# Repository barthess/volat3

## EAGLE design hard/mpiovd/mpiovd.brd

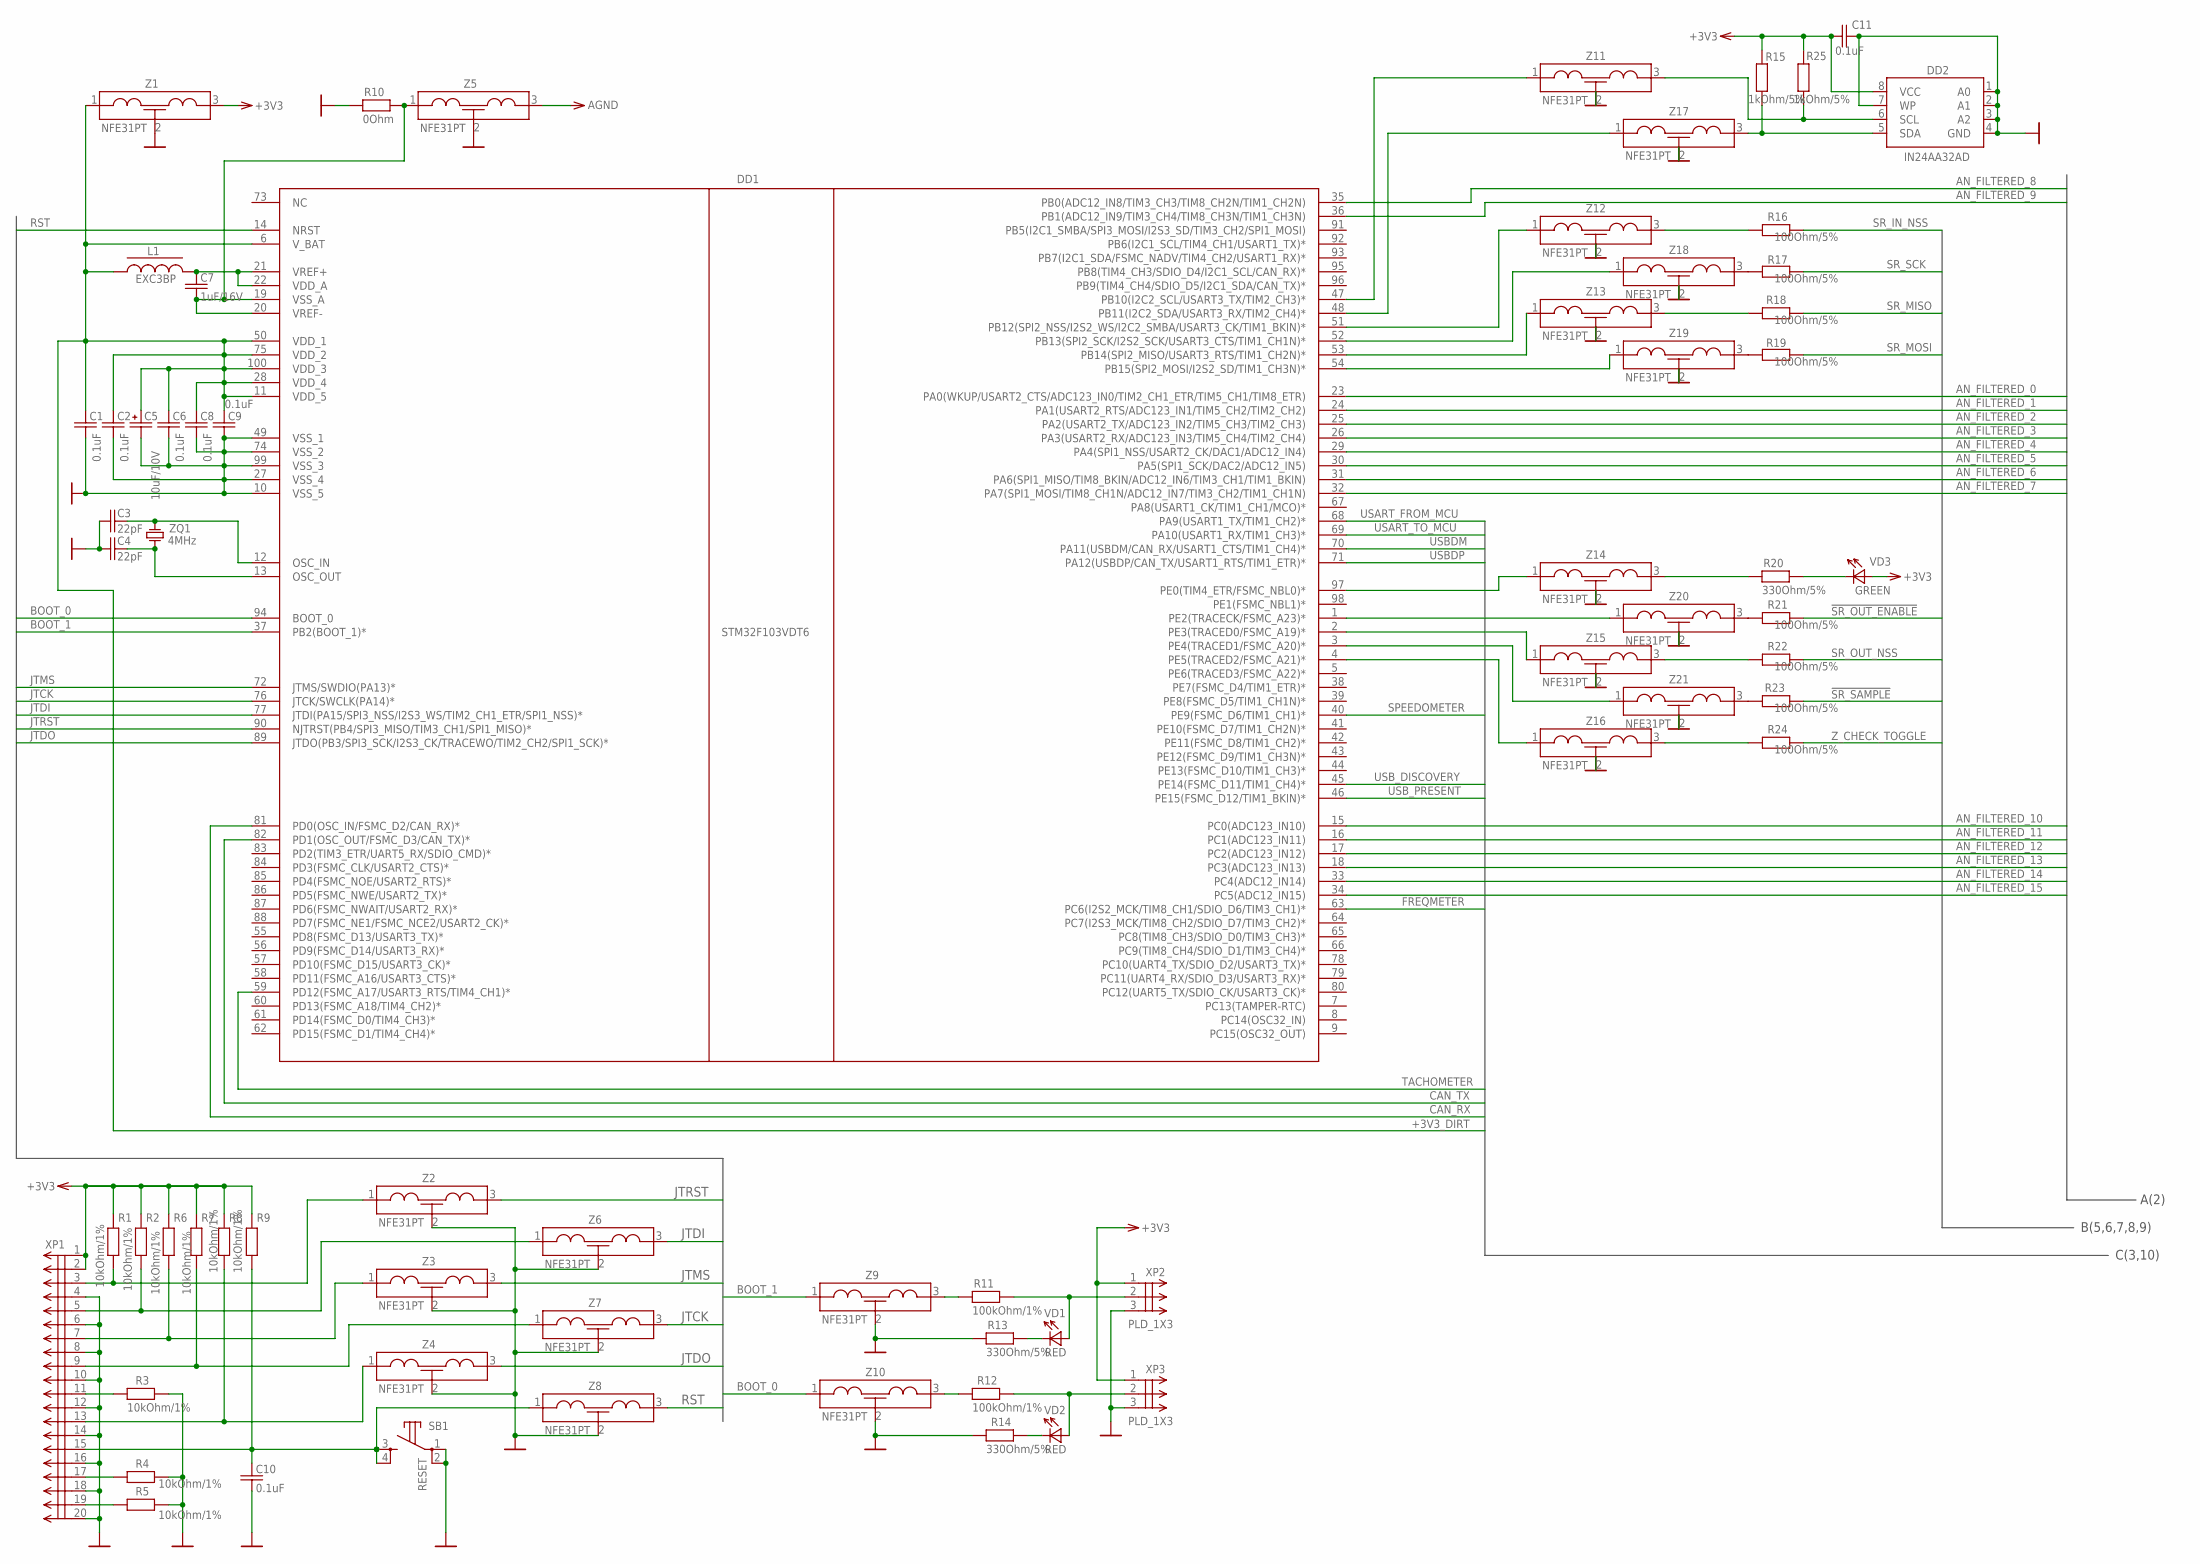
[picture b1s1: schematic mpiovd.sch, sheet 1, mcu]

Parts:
C1, C2, C6, C8, C9, C10, C11: 0.1uF; C0603; PARTNO C0603C104K5RACTU
C3, C4: 22pF; C0603; PARTNO C0603C220J5GACTU
C5: 10uF/10V; A/3216-18W; PARTNO T491A106K010AT
C7: 1uF/16V; C0603; PARTNO C0603C105K4PACTU
DD1: STM32F103VDT6; TQFP100; PARTNO STM32F103VDT6
DD2: IN24AA32AD; SO08; PARTNO IN24AA32AD
L1: EXC3BP; L0603; PARTNO EXC3BP121H
R1, R2, R3, R4, R5, R6, R7, R8, R9: 10kOhm/1%; R0603; PARTNO RC0603FR-1010KL
R10: 0Ohm; R0805; PARTNO ERJ6GEY0R00V
R11, R12: 100kOhm/1%; R0603; PARTNO RC0603FR-13100KL
R13, R14, R20: 330Ohm/5%; R0603; PARTNO ERJ3GEYJ331V
R15, R25: 1kOhm/5%; R0805; PARTNO ERJ6GEYJ102V
R16, R17, R18, R19, R21, R22, R23, R24: 100Ohm/5%; R0603; PARTNO ERJ3GEYJ101V
SB1: RESET; B3S-10XX; PARTNO 4-1437565-2
VD1, VD2: RED; LED-0805; PARTNO KPHCM-2012EC-T
VD3: GREEN; LED-0805; PARTNO KPHCM-2012SGC-T
XP1: PLD_2X10-SHROUDED; PLD_2X10_SHROUDED; PARTNO MC9A12-2034
XP2, XP3: PLD_1X3; PLD_1X03; PARTNO 825433-3
Z1, Z2, Z3, Z4, Z5, Z6, Z7, Z8, Z9, Z10, Z11, Z12, Z13, Z14, Z15, Z16, Z17, Z18, Z19, Z20, Z21: NFE31PT; NFE31; PARTNO NFE31PT152Z1E9
ZQ1: 4MHz; HC49U-V; PARTNO CA-4.000-18-3050-X

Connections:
!SR_OUT_ENABLE: R21.1; also elsewhere on the board
!SR_SAMPLE: R23.1; also elsewhere on the board
+3V3: C11.2, DD2.8 (VCC), R1.2, R2.2, R6.2, R7.2, R8.2, R9.2, R15.1, R25.1, VD3.A, XP1.1, XP1.2, XP2.1, XP3.1, Z1.3; also elsewhere on the board
+3V3_DIRT: C1.1, C2.1, C5.+, C6.1, C8.1, C9.1, DD1.6 (V_BAT), DD1.11 (VDD_5), DD1.28 (VDD_4), DD1.50 (VDD_1), DD1.75 (VDD_2), DD1.100 (VDD_3), L1.1, Z1.1; also elsewhere on the board
AGND: Z5.3; also elsewhere on the board
AN_FILTERED_0: DD1.23 (PA0(WKUP/USART2_CTS/ADC123_IN0/TIM2_CH1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); also elsewhere on the board
AN_FILTERED_1: DD1.24 (PA1(USART2_RTS/ADC123_IN1/TIM5_CH2/TIM2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); also elsewhere on the board
AN_FILTERED_2: DD1.25 (PA2(USART2_TX/ADC123_IN2/TIM5_CH3/TIM2_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); also elsewhere on the board
AN_FILTERED_3: DD1.26 (PA3(USART2_RX/ADC123_IN3/TIM5_CH4/TIM2_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); also elsewhere on the board
AN_FILTERED_4: DD1.29 (PA4(SPI1_NSS/USART2_CK/DAC1/ADC12_IN4)); also elsewhere on the board
AN_FILTERED_5: DD1.30 (PA5(SPI1_SCK/DAC2/ADC12_IN5)); also elsewhere on the board
AN_FILTERED_6: DD1.31 (PA6(SPI1_MISO/TIM8_BKIN/ADC12_IN6/TIM3_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); also elsewhere on the board
AN_FILTERED_7: DD1.32 (PA7(SPI1_MOSI/TIM8_CH1N/ADC12_IN7/TIM3_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); also elsewhere on the board
AN_FILTERED_8: DD1.35 (PB0(ADC12_IN8/TIM3_CH3/TIM8_CH2N/TIM1_C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); also elsewhere on the board
AN_FILTERED_9: DD1.36 (PB1(ADC12_IN9/TIM3_CH4/TIM8_CH3N/TIM1_C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); also elsewhere on the board
AN_FILTERED_10: DD1.15 (PC0(ADC123_IN10)); also elsewhere on the board
AN_FILTERED_11: DD1.16 (PC1(ADC123_IN11)); also elsewhere on the board
AN_FILTERED_12: DD1.17 (PC2(ADC123_IN12)); also elsewhere on the board
AN_FILTERED_13: DD1.18 (PC3(ADC123_IN13)); also elsewhere on the board
AN_FILTERED_14: DD1.33 (PC4(ADC12_IN14)); also elsewhere on the board
AN_FILTERED_15: DD1.34 (PC5(ADC12_IN15)); also elsewhere on the board
BOOT_0: DD1.94 (BOOT_0), Z10.1
BOOT_1: DD1.37 (PB2(BOOT_1)*), Z9.1
CAN_RX: DD1.81 (PD0(OSC_IN/FSMC_D2/CAN_RX)*); also elsewhere on the board
CAN_TX: DD1.82 (PD1(OSC_OUT/FSMC_D3/CAN_TX)*); also elsewhere on the board
FREQMETER: DD1.63 (PC6(I2S2_MCK/TIM8_CH1/SDIO_D6/TIM3_CH1)*); also elsewhere on the board
GND: C1.2, C2.2, C3.2, C4.2, C5.-, C6.2, C8.2, C9.2, C10.2, C11.1, DD1.10 (VSS_5), DD1.27 (VSS_4), DD1.49 (VSS_1), DD1.74 (VSS_2), DD1.99 (VSS_3), DD2.1 (A0), DD2.2 (A1), DD2.3 (A2), DD2.4 (GND), DD2.7 (WP), R3.2, R4.2, R5.2, R10.1, R13.1, R14.1, SB1.1, SB1.2, XP1.4, XP1.6, XP1.8, XP1.10, XP1.12, XP1.14, XP1.16, XP1.18, XP1.20, XP2.3, XP3.3, Z1.2, Z2.2, Z3.2, Z4.2, Z5.2, Z6.2, Z7.2, Z8.2, Z9.2, Z10.2, Z11.2, Z12.2, Z13.2, Z14.2, Z15.2, Z16.2, Z17.2, Z18.2, Z19.2, Z20.2, Z21.2; also elsewhere on the board
I2C_SCL: DD1.47 (PB10(I2C2_SCL/USART3_TX/TIM2_CH3)*), Z11.1
I2C_SDA: DD2.5 (SDA), R15.2, Z17.3
JTCK: DD1.76 (JTCK/SWCLK(PA14)*), Z7.3
JTDI: DD1.77 (JTDI(PA15/SPI3_NSS/I2S3_WS/TIM2_CH1_ETR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), Z6.3
JTDO: DD1.89 (JTDO(PB3/SPI3_SCK/I2S3_CK/TRACEWO/TIM2_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), Z4.3
JTMS: DD1.72 (JTMS/SWDIO(PA13)*), Z3.3
JTRST: DD1.90 (NJTRST(PB4/SPI3_MISO/TIM3_CH1/SPI1_MISO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), Z2.3
unnamed: R5.1, XP1.19
unnamed: R4.1, XP1.17
unnamed: C4.1, DD1.13 (OSC_OUT), ZQ1.1
unnamed: C3.1, DD1.12 (OSC_IN), ZQ1.2
unnamed: DD1.51 (PB12(SPI2_NSS/I2S2_WS/I2C2_SMBA/USART3_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), Z12.1
unnamed: R3.1, XP1.11
unnamed: R12.2, VD2.A, XP3.2
unnamed: R11.2, VD1.A, XP2.2
unnamed: R13.2, VD1.C
unnamed: DD1.52 (PB13(SPI2_SCK/I2S2_SCK/USART3_CTS/TIM1_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), Z18.1
unnamed: DD1.53 (PB14(SPI2_MISO/USART3_RTS/TIM1_CH2N)*), Z13.1
unnamed: DD1.54 (PB15(SPI2_MOSI/I2S2_SD/TIM1_CH3N)*), Z19.1
unnamed: DD1.1 (PE2(TRACECK/FSMC_A23)*), Z20.1
unnamed: C7.1, DD1.21 (VREF+), DD1.22 (VDD_A), L1.2
unnamed: R14.2, VD2.C
unnamed: R20.2, VD3.C
unnamed: R20.1, Z14.3
unnamed: DD1.2 (PE3(TRACED0/FSMC_A19)*), Z15.1
unnamed: DD1.3 (PE4(TRACED1/FSMC_A20)*), Z21.1
unnamed: DD1.4 (PE5(TRACED2/FSMC_A21)*), Z16.1
unnamed: C7.2, DD1.19 (VSS_A), DD1.20 (VREF-), R10.2, Z5.1
unnamed: R12.1, Z10.3
unnamed: R11.1, Z9.3
unnamed: R1.1, XP1.3, Z2.1
unnamed: R2.1, XP1.5, Z6.1
unnamed: R6.1, XP1.7, Z3.1
unnamed: C10.1, R9.1, SB1.3, SB1.4, XP1.15, Z8.1
unnamed: R7.1, XP1.9, Z7.1
unnamed: R8.1, XP1.13, Z4.1
unnamed: DD1.48 (PB11(I2C2_SDA/USART3_RX/TIM2_CH4)*), Z17.1
unnamed: DD2.6 (SCL), R25.2, Z11.3
unnamed: DD1.97 (PE0(TIM4_ETR/FSMC_NBL0)*), Z14.1
unnamed: R21.2, Z20.3
unnamed: R22.2, Z15.3
unnamed: R23.2, Z21.3
unnamed: R24.2, Z16.3
unnamed: R16.2, Z12.3
unnamed: R18.2, Z13.3
unnamed: R17.2, Z18.3
unnamed: R19.2, Z19.3
RST: DD1.14 (NRST), Z8.3
SPEEDOMETER: DD1.40 (PE9(FSMC_D6/TIM1_CH1)*); also elsewhere on the board
SR_IN_NSS: R16.1; also elsewhere on the board
SR_MISO: R18.1; also elsewhere on the board
SR_MOSI: R19.1; also elsewhere on the board
SR_OUT_NSS: R22.1; also elsewhere on the board
SR_SCK: R17.1; also elsewhere on the board
TACHOMETER: DD1.59 (PD12(FSMC_A17/USART3_RTS/TIM4_CH1)*); also elsewhere on the board
USART_FROM_MCU: DD1.68 (PA9(USART1_TX/TIM1_CH2)*); also elsewhere on the board
USART_TO_MCU: DD1.69 (PA10(USART1_RX/TIM1_CH3)*); also elsewhere on the board
USBDM: DD1.70 (PA11(USBDM/CAN_RX/USART1_CTS/TIM1_CH4)*); also elsewhere on the board
USBDP: DD1.71 (PA12(USBDP/CAN_TX/USART1_RTS/TIM1_ETR)*); also elsewhere on the board
USB_DISCOVERY: DD1.45 (PE14(FSMC_D11/TIM1_CH4)*); also elsewhere on the board
USB_PRESENT: DD1.46 (PE15(FSMC_D12/TIM1_BKIN)*); also elsewhere on the board
Z_CHECK_TOGGLE: R24.1; also elsewhere on the board

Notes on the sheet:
A(2)
C(3,10)
B(5,6,7,8,9)

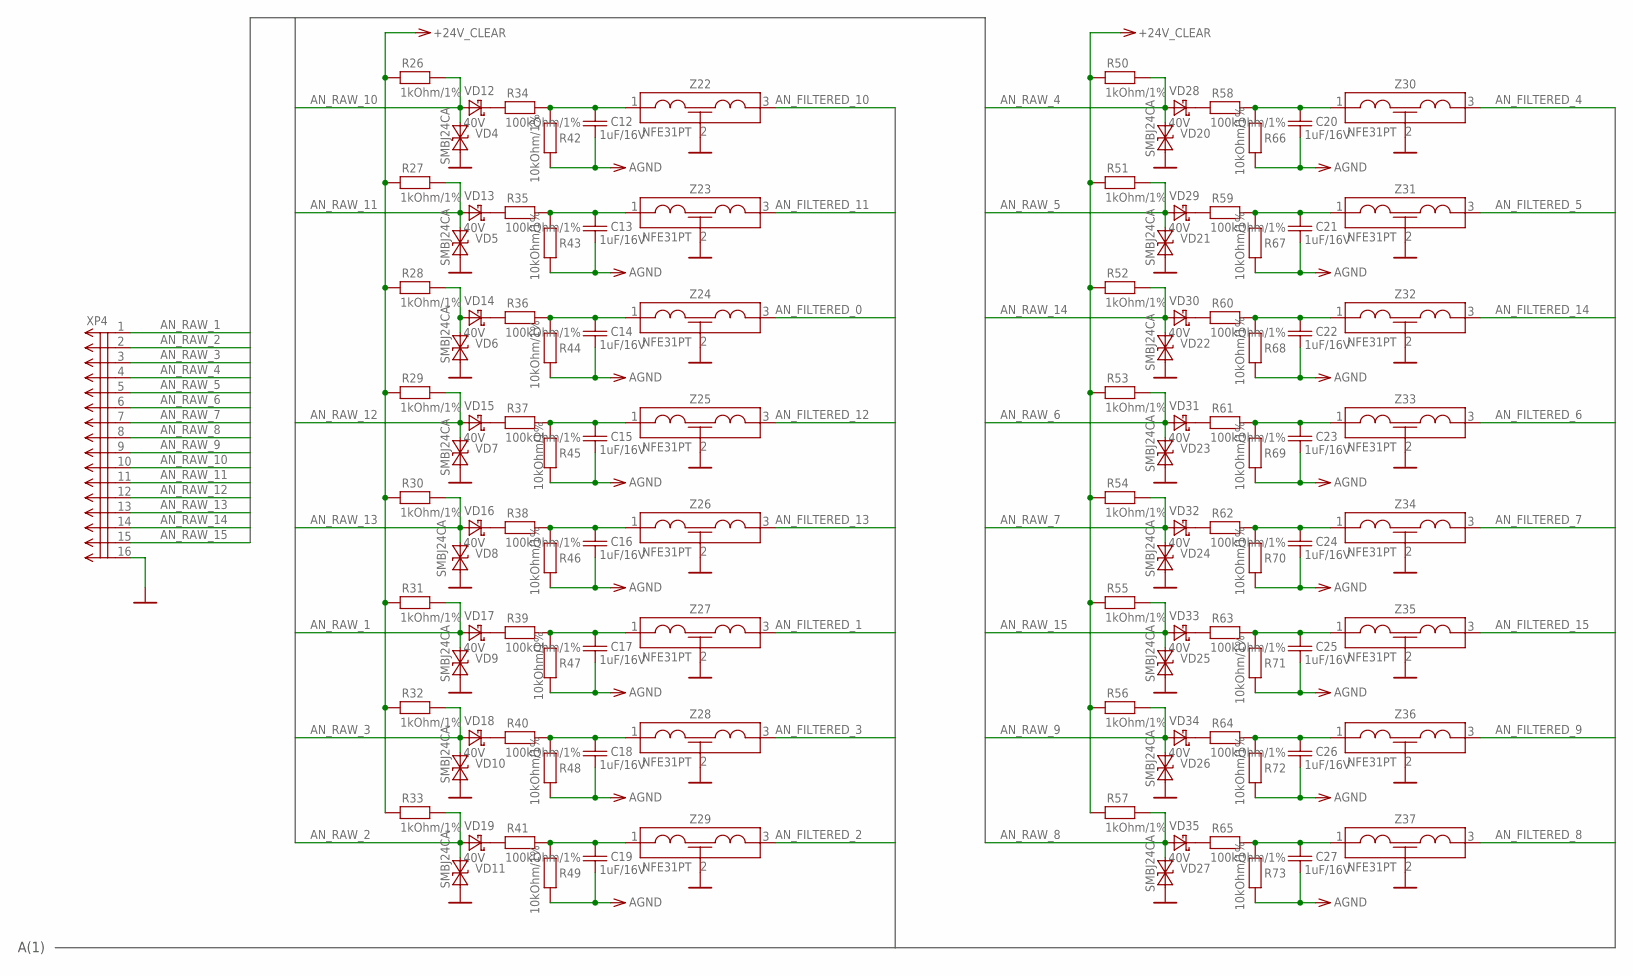
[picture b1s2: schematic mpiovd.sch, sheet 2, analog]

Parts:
C12, C13, C14, C15, C16, C17, C18, C19, C20, C21, C22, C23, C24, C25, C26, C27: 1uF/16V; C0603; PARTNO C0603C105K4PACTU
R26, R27, R28, R29, R30, R31, R32, R33, R50, R51, R52, R53, R54, R55, R56, R57: 1kOhm/1%; R2512; PARTNO RC2512FK-071KL
R34, R35, R36, R37, R38, R39, R40, R41, R58, R59, R60, R61, R62, R63, R64, R65: 100kOhm/1%; R0603; PARTNO RC0603FR-13100KL
R42, R43, R44, R45, R46, R47, R48, R49, R66, R67, R68, R69, R70, R71, R72, R73: 10kOhm/1%; R0603; PARTNO RC0603FR-1010KL
VD4, VD5, VD6, VD7, VD8, VD9, VD10, VD11, VD20, VD21, VD22, VD23, VD24, VD25, VD26, VD27: SMBJ24CA; SMB-BIDIR; PARTNO SMBJ24CA
VD12, VD13, VD14, VD15, VD16, VD17, VD18, VD19, VD28, VD29, VD30, VD31, VD32, VD33, VD34, VD35: 40V; SOD323; PARTNO BAT54JFILM
XP4: MOLEX-90130-16; PARTNO 90130-1216
Z22, Z23, Z24, Z25, Z26, Z27, Z28, Z29, Z30, Z31, Z32, Z33, Z34, Z35, Z36, Z37: NFE31PT; NFE31; PARTNO NFE31PT152Z1E9

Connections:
+24V_CLEAR: R26.1, R27.1, R28.1, R29.1, R30.1, R31.1, R32.1, R33.1, R50.1, R51.1, R52.1, R53.1, R54.1, R55.1, R56.1, R57.1; also elsewhere on the board
AGND: C12.2, C13.2, C14.2, C15.2, C16.2, C17.2, C18.2, C19.2, C20.2, C21.2, C22.2, C23.2, C24.2, C25.2, C26.2, C27.2, R42.1, R43.1, R44.1, R45.1, R46.1, R47.1, R48.1, R49.1, R66.1, R67.1, R68.1, R69.1, R70.1, R71.1, R72.1, R73.1; also elsewhere on the board
AN_FILTERED_0: Z24.3; also elsewhere on the board
AN_FILTERED_1: Z27.3; also elsewhere on the board
AN_FILTERED_2: Z29.3; also elsewhere on the board
AN_FILTERED_3: Z28.3; also elsewhere on the board
AN_FILTERED_4: Z30.3; also elsewhere on the board
AN_FILTERED_5: Z31.3; also elsewhere on the board
AN_FILTERED_6: Z33.3; also elsewhere on the board
AN_FILTERED_7: Z34.3; also elsewhere on the board
AN_FILTERED_8: Z37.3; also elsewhere on the board
AN_FILTERED_9: Z36.3; also elsewhere on the board
AN_FILTERED_10: Z22.3; also elsewhere on the board
AN_FILTERED_11: Z23.3; also elsewhere on the board
AN_FILTERED_12: Z25.3; also elsewhere on the board
AN_FILTERED_13: Z26.3; also elsewhere on the board
AN_FILTERED_14: Z32.3; also elsewhere on the board
AN_FILTERED_15: Z35.3; also elsewhere on the board
AN_RAW_1: R31.2, VD9.A1, VD17.A, XP4.1
AN_RAW_2: R33.2, VD11.A1, VD19.A, XP4.2
AN_RAW_2_SUPPLY: R28.2, VD6.A1, VD14.A
AN_RAW_3: R32.2, VD10.A1, VD18.A, XP4.3
AN_RAW_4: R50.2, VD20.A1, VD28.A, XP4.4
AN_RAW_5: R51.2, VD21.A1, VD29.A, XP4.5
AN_RAW_6: R53.2, VD23.A1, VD31.A, XP4.6
AN_RAW_7: R54.2, VD24.A1, VD32.A, XP4.7
AN_RAW_8: R57.2, VD27.A1, VD35.A, XP4.8
AN_RAW_9: R56.2, VD26.A1, VD34.A, XP4.9
AN_RAW_10: R26.2, VD4.A1, VD12.A, XP4.10
AN_RAW_11: R27.2, VD5.A1, VD13.A, XP4.11
AN_RAW_12: R29.2, VD7.A1, VD15.A, XP4.12
AN_RAW_13: R30.2, VD8.A1, VD16.A, XP4.13
AN_RAW_14: R52.2, VD22.A1, VD30.A, XP4.14
AN_RAW_15: R55.2, VD25.A1, VD33.A, XP4.15
GND: VD4.A2, VD5.A2, VD6.A2, VD7.A2, VD8.A2, VD9.A2, VD10.A2, VD11.A2, VD20.A2, VD21.A2, VD22.A2, VD23.A2, VD24.A2, VD25.A2, VD26.A2, VD27.A2, XP4.16, Z22.2, Z23.2, Z24.2, Z25.2, Z26.2, Z27.2, Z28.2, Z29.2, Z30.2, Z31.2, Z32.2, Z33.2, Z34.2, Z35.2, Z36.2, Z37.2; also elsewhere on the board
unnamed: R34.1, VD12.C
unnamed: R35.1, VD13.C
unnamed: R41.1, VD19.C
unnamed: R40.1, VD18.C
unnamed: R39.1, VD17.C
unnamed: R38.1, VD16.C
unnamed: R37.1, VD15.C
unnamed: R36.1, VD14.C
unnamed: R58.1, VD28.C
unnamed: R60.1, VD30.C
unnamed: R59.1, VD29.C
unnamed: R61.1, VD31.C
unnamed: R62.1, VD32.C
unnamed: R64.1, VD34.C
unnamed: R63.1, VD33.C
unnamed: R65.1, VD35.C
unnamed: C12.1, R34.2, R42.2, Z22.1
unnamed: C13.1, R35.2, R43.2, Z23.1
unnamed: C14.1, R36.2, R44.2, Z24.1
unnamed: C15.1, R37.2, R45.2, Z25.1
unnamed: C16.1, R38.2, R46.2, Z26.1
unnamed: C17.1, R39.2, R47.2, Z27.1
unnamed: C18.1, R40.2, R48.2, Z28.1
unnamed: C19.1, R41.2, R49.2, Z29.1
unnamed: C20.1, R58.2, R66.2, Z30.1
unnamed: C21.1, R59.2, R67.2, Z31.1
unnamed: C22.1, R60.2, R68.2, Z32.1
unnamed: C23.1, R61.2, R69.2, Z33.1
unnamed: C24.1, R62.2, R70.2, Z34.1
unnamed: C25.1, R63.2, R71.2, Z35.1
unnamed: C26.1, R64.2, R72.2, Z36.1
unnamed: C27.1, R65.2, R73.2, Z37.1

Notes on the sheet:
A(1)

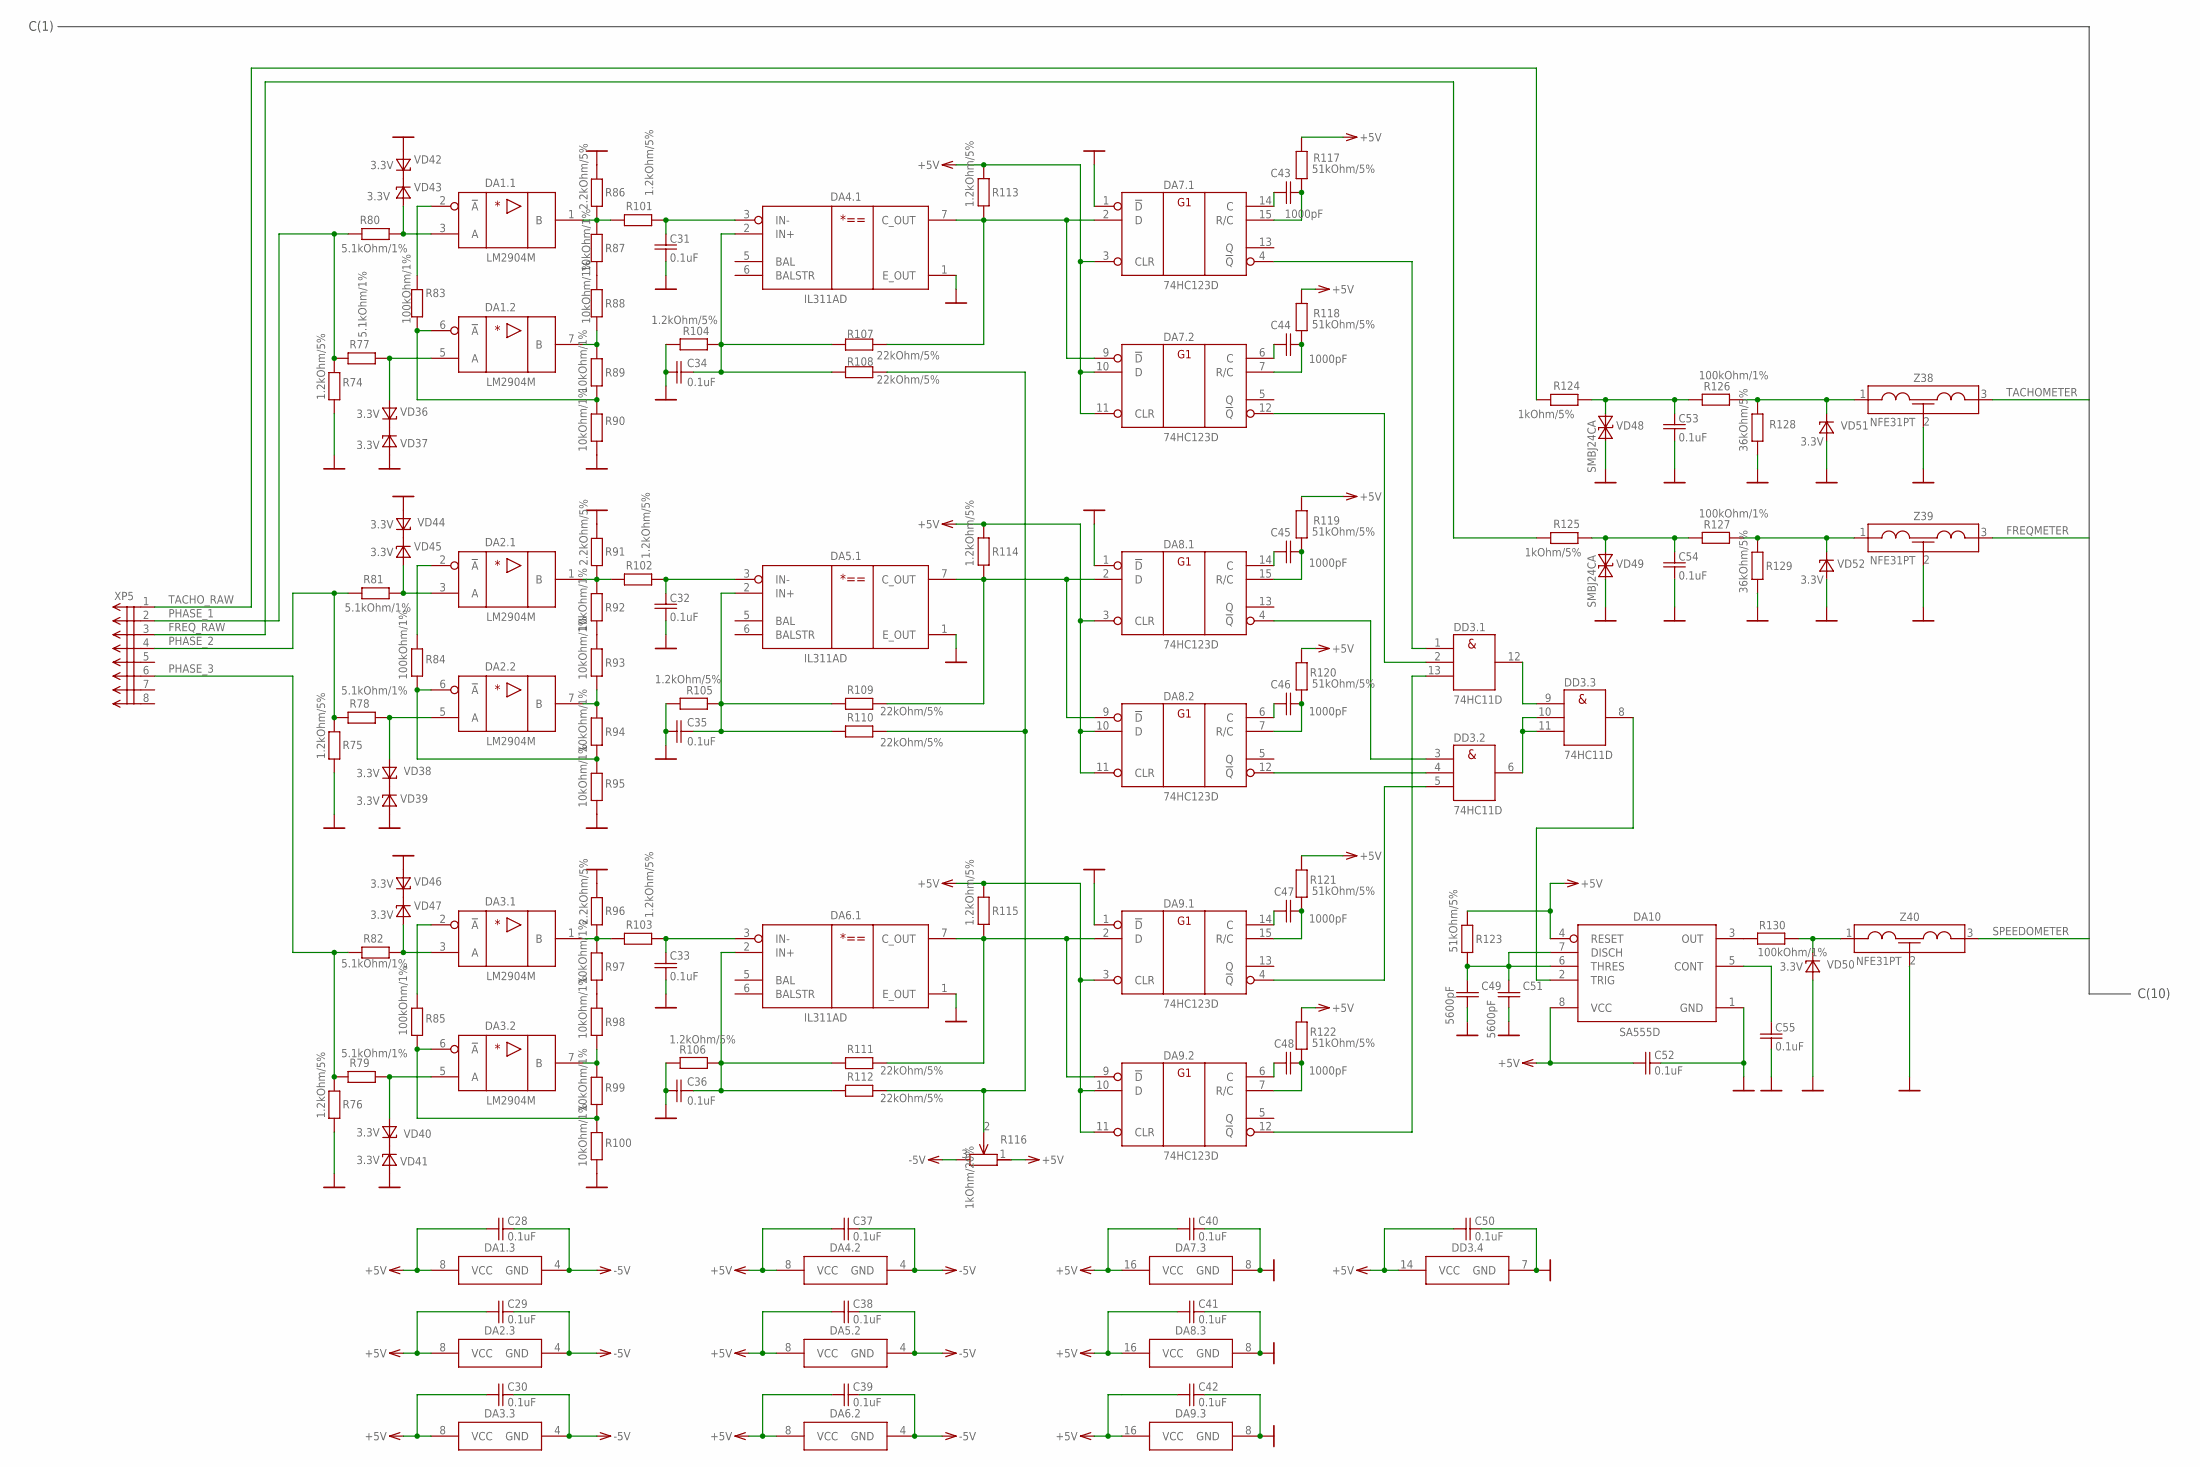
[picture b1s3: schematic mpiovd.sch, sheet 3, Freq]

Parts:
C28, C29, C30, C31, C32, C33, C34, C35, C36, C37, C38, C39, C40, C41, C42, C50, C52, C53, C54, C55: 0.1uF; C0603; PARTNO C0603C104K5RACTU
C43, C44, C45, C46, C47, C48: 1000pF; C0603; PARTNO C0603C102K5RACTU
C49, C51: 5600pF; C0603; PARTNO C0603C562K5RACTU
DA1, DA2, DA3: LM2904M; SO08; PARTNO LM2904M
DA4, DA5, DA6: IL311AD; SO08; PARTNO IL311AD
DA7, DA8, DA9: 74HC123D; SO16; PARTNO IN74HC123AD
DA10: SA555D; SO08; PARTNO SA555D
DD3: 74HC11D; SO14; PARTNO IN74HC11AD
R74, R75, R76, R101, R102, R103, R104, R105, R106, R113, R114, R115: 1.2kOhm/5%; R0603; PARTNO RC0603JR-071K2L
R77, R78, R79, R80, R81, R82: 5.1kOhm/1%; R0603; PARTNO RC0603FR-075K1L
R83, R84, R85, R126, R127, R130: 100kOhm/1%; R0603; PARTNO RC0603FR-13100KL
R86, R91, R96: 2.2kOhm/5%; R0603; PARTNO RC0603JR-072K2L
R87, R88, R89, R90, R92, R93, R94, R95, R97, R98, R99, R100: 10kOhm/1%; R0603; PARTNO RC0603FR-1010KL
R107, R108, R109, R110, R111, R112: 22kOhm/5%; R0603; PARTNO RC0603JR-0722KL
R116: 1kOhm/20%; RTRIMTSM53YJ; PARTNO TSM4YJ102KR05
R117, R118, R119, R120, R121, R122, R123: 51kOhm/5%; R0603; PARTNO RC0603JR-0751KL
R124, R125: 1kOhm/5%; R2512; PARTNO RC2512JK-071KL
R128, R129: 36kOhm/5%; R0603; PARTNO ERJ3GEYJ363V
VD36, VD37, VD38, VD39, VD40, VD41, VD42, VD43, VD44, VD45, VD46, VD47, VD50, VD51, VD52: 3.3V; SOD80; PARTNO BZV55-C3V3
VD48, VD49: SMBJ24CA; SMB-BIDIR; PARTNO SMBJ24CA
XP5: MOLEX-90130-08; PARTNO 90130-1208
Z38, Z39, Z40: NFE31PT; NFE31; PARTNO NFE31PT152Z1E9

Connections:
+5V: C28.1, C29.1, C30.1, C37.1, C38.1, C39.1, C40.1, C41.1, C42.1, C50.1, C52.1, DA1.8 (VCC), DA2.8 (VCC), DA3.8 (VCC), DA4.8 (VCC), DA5.8 (VCC), DA6.8 (VCC), DA7.3 (CLR), DA7.10 (D), DA7.11 (CLR), DA7.16 (VCC), DA8.3 (CLR), DA8.10 (D), DA8.11 (CLR), DA8.16 (VCC), DA9.3 (CLR), DA9.10 (D), DA9.11 (CLR), DA9.16 (VCC), DA10.4 (RESET), DA10.8 (VCC), DD3.14 (VCC), R113.1, R114.1, R115.1, R116.1 (A), R117.2, R118.2, R119.2, R120.2, R121.2, R122.2, R123.2; also elsewhere on the board
-5V: C28.2, C29.2, C30.2, C37.2, C38.2, C39.2, DA1.4 (GND), DA2.4 (GND), DA3.4 (GND), DA4.4 (GND), DA5.4 (GND), DA6.4 (GND), R116.3 (E); also elsewhere on the board
FREQMETER: Z39.3; also elsewhere on the board
FREQ_RAW: R125.2, XP5.3
GND: C31.1, C32.1, C33.1, C34.2, C35.2, C36.2, C40.2, C41.2, C42.2, C49.2, C50.2, C51.2, C52.2, C53.1, C54.1, C55.2, DA4.1 (E_OUT), DA5.1 (E_OUT), DA6.1 (E_OUT), DA7.1 (!D), DA7.8 (GND), DA8.1 (!D), DA8.8 (GND), DA9.1 (!D), DA9.8 (GND), DA10.1 (GND), DD3.7 (GND), R74.1, R75.1, R76.1, R86.2, R90.1, R91.2, R95.1, R96.2, R100.1, R104.2, R105.2, R106.2, R128.1, R129.1, VD37.A, VD39.A, VD41.A, VD42.A, VD44.A, VD46.A, VD48.A2, VD49.A2, VD50.A, VD51.A, VD52.A, Z38.2, Z39.2, Z40.2; also elsewhere on the board
unnamed: VD44.C, VD45.C
unnamed: C53.2, R124.1, R126.1, VD48.A1
unnamed: DD3.6 (Y), DD3.10 (B), DD3.11 (C)
unnamed: DD3.9 (A), DD3.12 (Y)
unnamed: DA10.2 (TRIG), DD3.8 (Y)
unnamed: DA10.3 (OUT), R130.1
unnamed: C34.1, DA4.2 (IN+), R104.1, R107.1, R108.1
unnamed: DA4.7 (C_OUT), DA7.2 (D), DA7.9 (!D), R107.2, R113.2
unnamed: VD42.C, VD43.C
unnamed: DA1.3 (A), R80.2, VD43.A
unnamed: C43.2, DA7.15 (R/C), R117.1
unnamed: DA2.3 (A), R81.2, VD45.A
unnamed: VD36.C, VD37.C
unnamed: DA1.5 (A), R77.2, VD36.A
unnamed: C43.1, DA7.14 (C)
unnamed: C44.1, DA7.6 (C)
unnamed: C31.2, DA4.3 (IN-), R101.2
unnamed: C44.2, DA7.7 (R/C), R118.1
unnamed: C49.1, C51.1, DA10.6 (THRES), DA10.7 (DISCH), R123.1
unnamed: DA1.2 (!A), R83.2
unnamed: DA7.4 (!Q), DD3.1 (A)
unnamed: DA7.12 (!Q), DD3.2 (B)
unnamed: C55.1, DA10.5 (CONT)
unnamed: DA1.7 (B), R88.1, R89.2
unnamed: DA1.6 (!A), R83.1, R89.1, R90.2
unnamed: R87.1, R88.2
unnamed: DA1.1 (B), R86.1, R87.2, R101.1
unnamed: VD38.C, VD39.C
unnamed: DA2.5 (A), R78.2, VD38.A
unnamed: DA2.2 (!A), R84.2
unnamed: DA2.7 (B), R93.1, R94.2
unnamed: DA2.6 (!A), R84.1, R94.1, R95.2
unnamed: R92.1, R93.2
unnamed: DA2.1 (B), R91.1, R92.2, R102.1
unnamed: C32.2, DA5.3 (IN-), R102.2
unnamed: C35.1, DA5.2 (IN+), R105.1, R109.1, R110.1
unnamed: DA5.7 (C_OUT), DA8.2 (D), DA8.9 (!D), R109.2, R114.2
unnamed: C45.2, DA8.15 (R/C), R119.1
unnamed: C45.1, DA8.14 (C)
unnamed: C46.2, DA8.7 (R/C), R120.1
unnamed: DA8.4 (!Q), DD3.3 (A)
unnamed: DA8.12 (!Q), DD3.4 (B)
unnamed: C46.1, DA8.6 (C)
unnamed: VD46.C, VD47.C
unnamed: DA3.3 (A), R82.2, VD47.A
unnamed: VD40.C, VD41.C
unnamed: DA3.5 (A), R79.2, VD40.A
unnamed: DA3.2 (!A), R85.2
unnamed: DA3.7 (B), R98.1, R99.2
unnamed: DA3.6 (!A), R85.1, R99.1, R100.2
unnamed: R97.1, R98.2
unnamed: DA3.1 (B), R96.1, R97.2, R103.1
unnamed: C33.2, DA6.3 (IN-), R103.2
unnamed: C36.1, DA6.2 (IN+), R106.1, R111.1, R112.1
unnamed: DA6.7 (C_OUT), DA9.2 (D), DA9.9 (!D), R111.2, R115.2
unnamed: C47.2, DA9.15 (R/C), R121.1
unnamed: C47.1, DA9.14 (C)
unnamed: C48.2, DA9.7 (R/C), R122.1
unnamed: DA9.4 (!Q), DD3.5 (C)
unnamed: DA9.12 (!Q), DD3.13 (C)
unnamed: C48.1, DA9.6 (C)
unnamed: R108.2, R110.2, R112.2, R116.2 (S)
unnamed: C54.2, R125.1, R127.1, VD49.A1
unnamed: R126.2, R128.2, VD51.C, Z38.1
unnamed: R127.2, R129.2, VD52.C, Z39.1
unnamed: R130.2, VD50.C, Z40.1
PHASE_1: R74.2, R77.1, R80.1, XP5.2
PHASE_2: R75.2, R78.1, R81.1, XP5.4
PHASE_3: R76.2, R79.1, R82.1, XP5.6
SPEEDOMETER: Z40.3; also elsewhere on the board
TACHOMETER: Z38.3; also elsewhere on the board
TACHO_RAW: R124.2, XP5.1

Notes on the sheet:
C(1)
C(10)

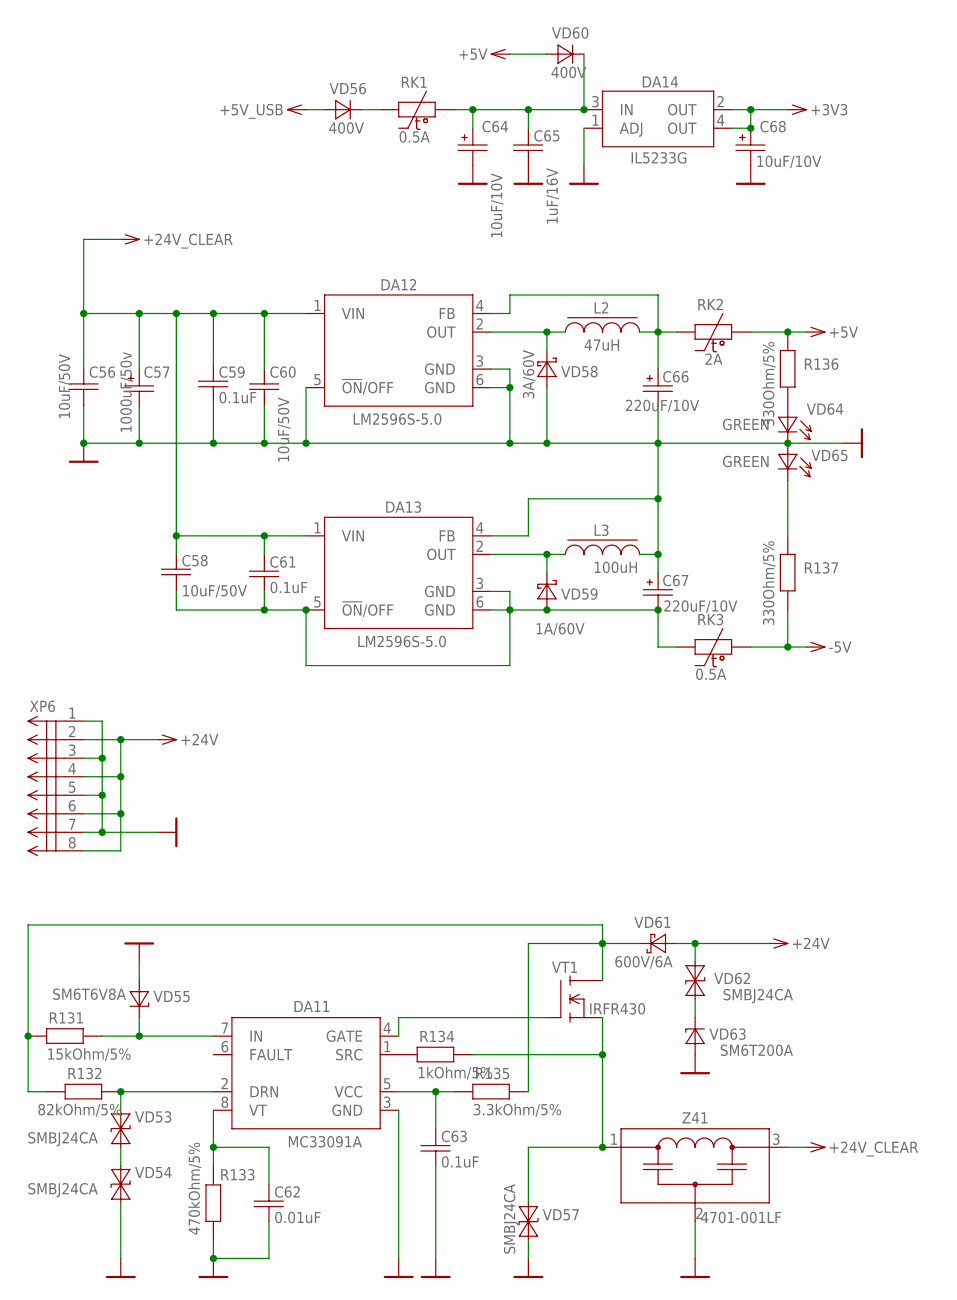
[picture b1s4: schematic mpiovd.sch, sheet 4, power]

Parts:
C56, C58, C60: 10uF/50V; C2220K; PARTNO 22205C106KAT2A
C57: 1000uF/50v; E35-16-STRAPPED; PARTNO 516D108M050QS6AE3
C59, C61, C63: 0.1uF; C0603; PARTNO C0603C104K5RACTU
C62: 0.01uF; C0603; PARTNO C0603C103K5RACTU
C64, C68: 10uF/10V; A/3216-18W; PARTNO T491A106K010AT
C65: 1uF/16V; C0603; PARTNO C0603C105K4PACTU
C66, C67: 220uF/10V; TE-D-7343; PARTNO T491D227K010AT
DA11: MC33091A; SO08; PARTNO IL33091AD
DA12, DA13: LM2596S-5.0; TO263-5; PARTNO LM2596S-5.0/NOPB
DA14: IL5233G; SOT223; PARTNO IL5233G
L2: 47uH; DRA127; PARTNO DR127-470-R
L3: 100uH; DRA73; PARTNO DR73-101-R
R131: 15kOhm/5%; R0805; PARTNO ERJ6GEYJ153V
R132: 82kOhm/5%; R0805; PARTNO RC0805JR-0782KL
R133: 470kOhm/5%; R0805; PARTNO ERJ6GEYJ474V
R134: 1kOhm/5%; R0805; PARTNO ERJ6GEYJ102V
R135: 3.3kOhm/5%; R2512; PARTNO 35203K3JT
R136, R137: 330Ohm/5%; R0603; PARTNO ERJ3GEYJ331V
RK1, RK3: 0.5A; RK1210; PARTNO 1210L050YR
RK2: 2A; RK1812; PARTNO 1812L200DR
VD53, VD54, VD57, VD62: SMBJ24CA; SMB-BIDIR; PARTNO SMBJ24CA
VD55: SM6T6V8A; SMB; PARTNO SM6T6V8A
VD56, VD60: 400V; SMA; PARTNO S1G-E3/61T
VD58: 3A/60V; SMC; PARTNO VS-30BQ060TRPBF
VD59: 1A/60V; SMB; PARTNO VS-10BQ060TRPBF
VD61: 600V/6A; DPAK; PARTNO IDD06SG60C
VD63: SM6T200A; SMB; PARTNO SM6T200A
VD64, VD65: GREEN; LED-0805; PARTNO KPHCM-2012SGC-T
VT1: IRFR430; DPAK; PARTNO IRFR430APBF
XP6: MOLEX-90130-08; PARTNO 90130-1208
Z41: 4701-001LF; TUSONIX-4701; PARTNO 4701-001LF

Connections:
+3V3: C68.+, DA14.2 (OUT), DA14.4 (OUT); also elsewhere on the board
+5V: R136.1, RK2.2, VD60.A; also elsewhere on the board
+5V_USB: VD56.A; also elsewhere on the board
+24V: VD61.3 (A), VD62.A1, XP6.2, XP6.4, XP6.6, XP6.8
+24V_CLEAR: C56.2, C57.+, C58.2, C59.1, C60.2, C61.1, DA12.1 (VIN), DA13.1 (VIN), Z41.3; also elsewhere on the board
-5V: R137.2, RK3.2; also elsewhere on the board
GND: C56.1, C57.-, C59.2, C60.1, C62.2, C63.2, C64.-, C65.2, C66.-, C67.+, C68.-, DA11.3 (GND), DA12.3 (GND), DA12.5 (!ON!/OFF), DA12.6 (GND), DA13.4 (FB), DA14.1 (ADJ), L3.2, R133.1, VD54.A1, VD55.A, VD57.A2, VD58.A, VD63.A, VD64.C, VD65.A, XP6.1, XP6.3, XP6.5, XP6.7, Z41.2; also elsewhere on the board
unnamed: DA12.2 (OUT), L2.1, VD58.C
unnamed: DA13.2 (OUT), L3.1, VD59.C
unnamed: C63.1, DA11.5 (VCC), R135.1
unnamed: VD62.A2, VD63.C
unnamed: VD53.A1, VD54.A2
unnamed: DA11.2 (DRN), R132.2, VD53.A2
unnamed: DA11.7 (IN), R131.2, VD55.C
unnamed: R131.1, R132.1, R135.2, VD61.2 (C), VT1.2 (D)
unnamed: DA11.1 (SRC), R134.1
unnamed: C62.1, DA11.8 (VT), R133.2
unnamed: DA11.4 (GATE), VT1.1 (G)
unnamed: C66.+, DA12.4 (FB), L2.2, RK2.1
unnamed: C58.1, C61.2, C67.-, DA13.3 (GND), DA13.5 (!ON!/OFF), DA13.6 (GND), RK3.1, VD59.A
unnamed: RK1.1, VD56.C
unnamed: C64.+, C65.1, DA14.3 (IN), RK1.2, VD60.C
unnamed: R134.2, VD57.A1, VT1.3 (S), Z41.1
unnamed: R136.2, VD64.A
unnamed: R137.1, VD65.C

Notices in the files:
parts and their libraries:
SparkFun: Licensing: CC v3.0 Share-Alike You are welcome to use this library for commercial purposes.
inductor-cooper: Copyright (C) 2010, Bob Starr
